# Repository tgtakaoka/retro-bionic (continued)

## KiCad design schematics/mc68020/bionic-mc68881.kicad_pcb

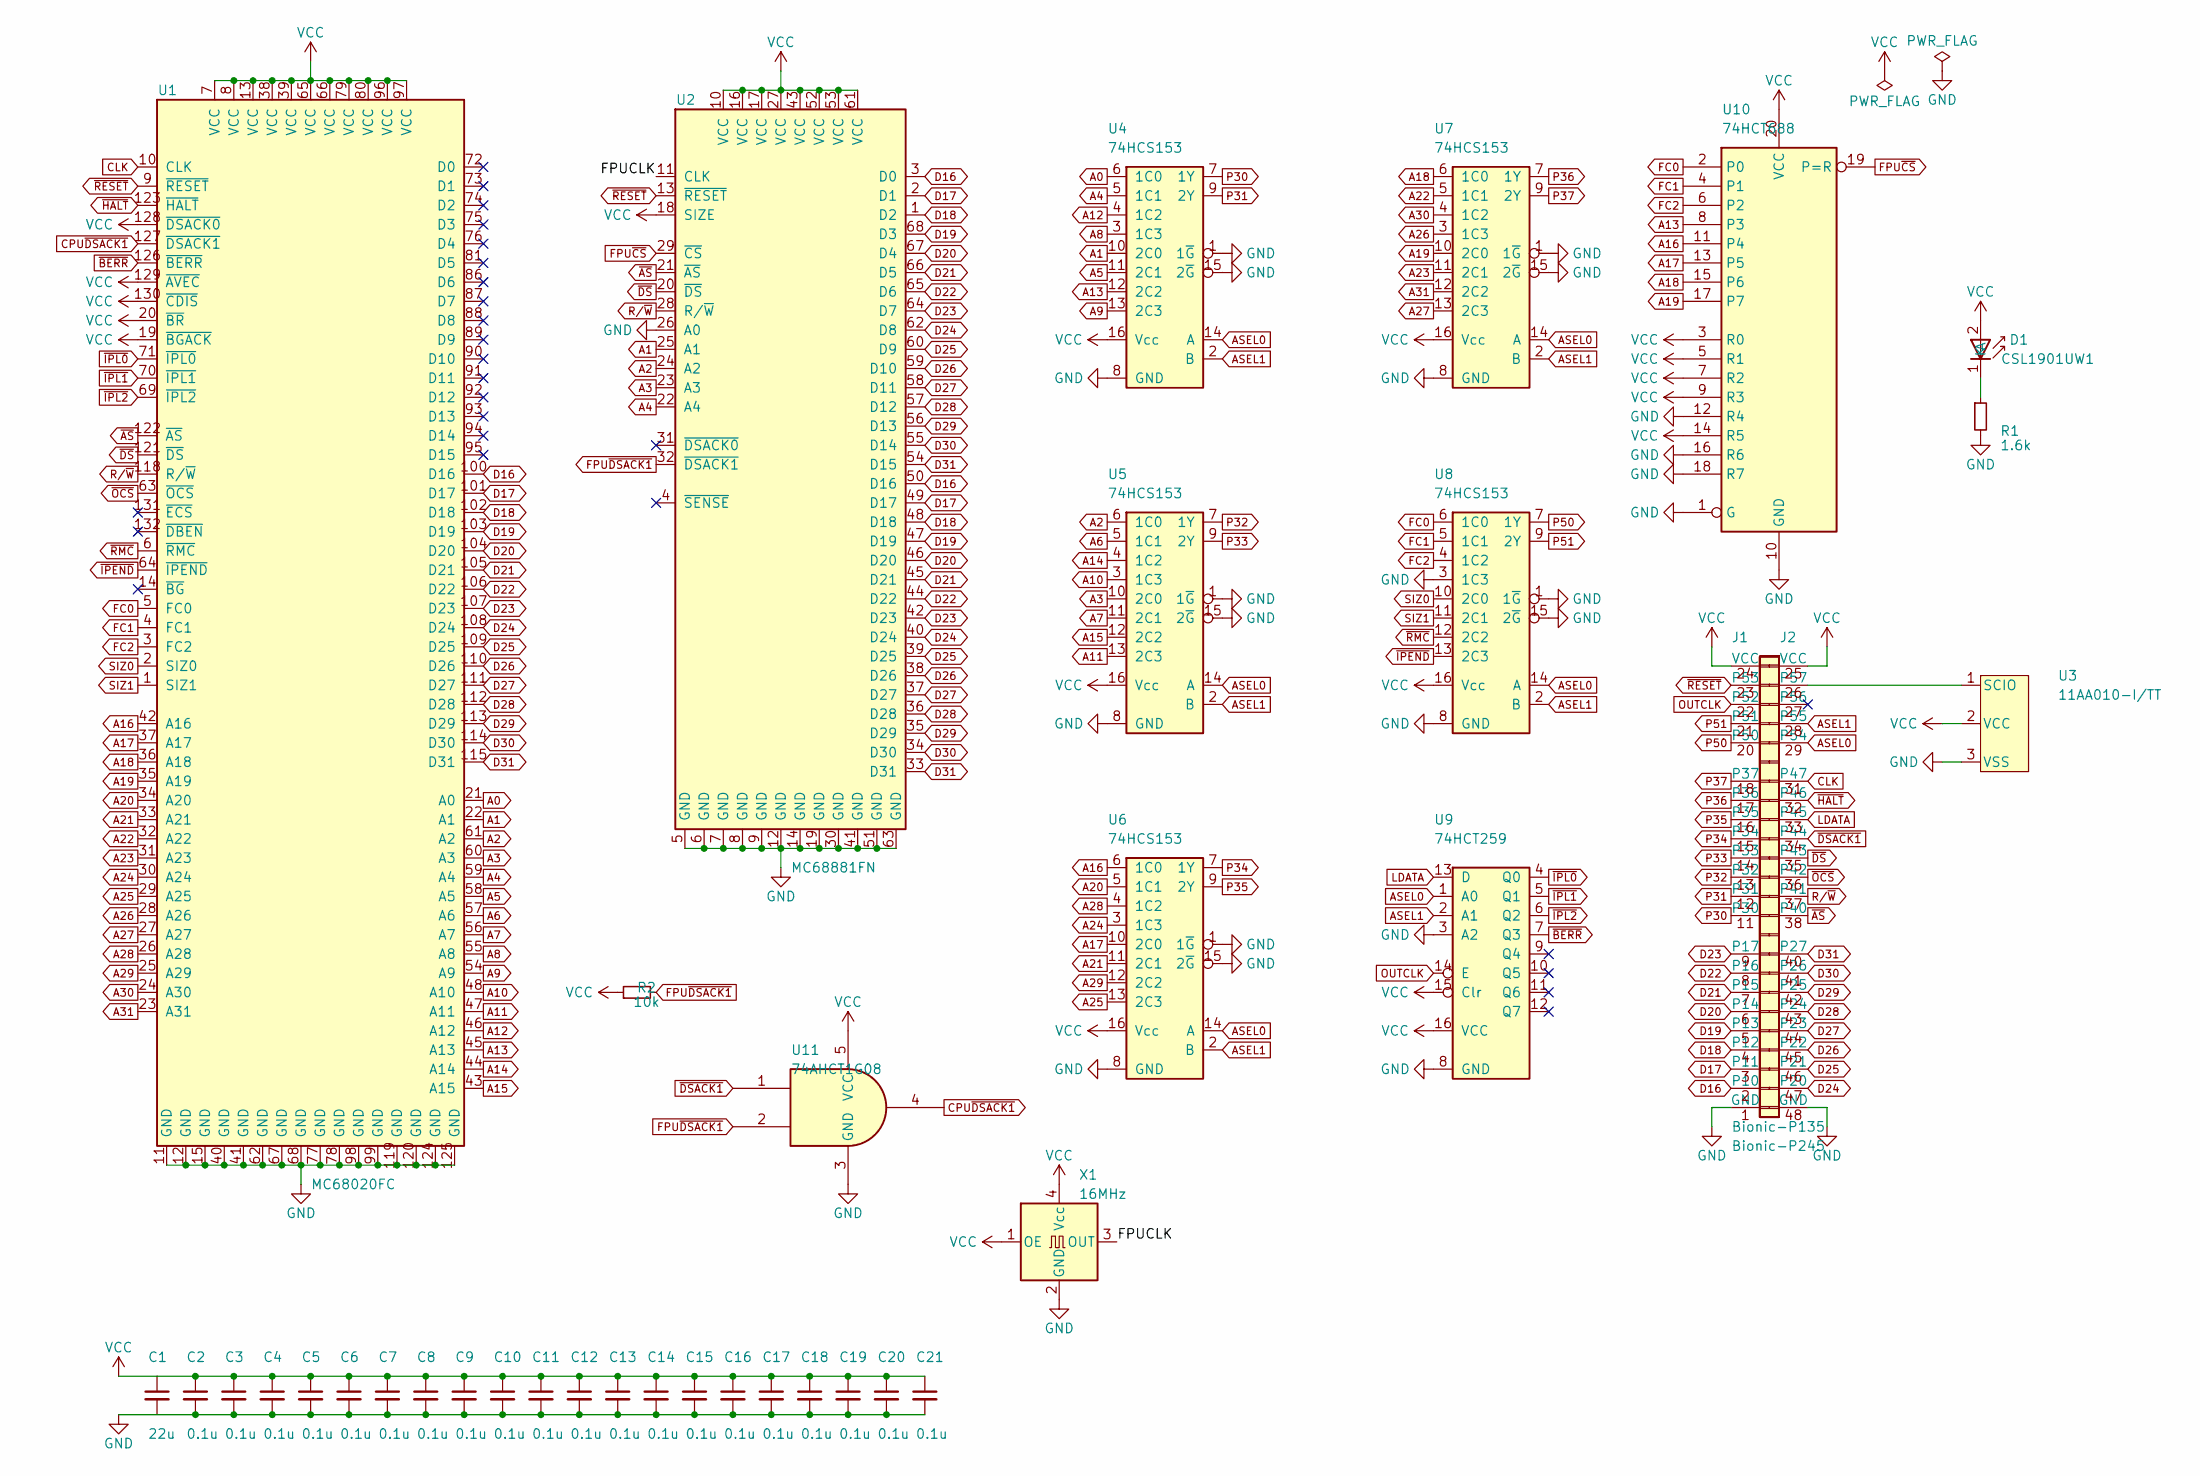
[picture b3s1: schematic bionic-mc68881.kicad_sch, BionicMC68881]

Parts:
C1: 22u; C_0603_1608Metric_Pad1.08x0.95mm_HandSolder
C2, C3, C4, C5, C6, C7, C8, C9, C10, C11, C12, C13, C14, C15, C16, C17, C18, C19, C20, C21: 0.1u; C_0603_1608Metric_Pad1.08x0.95mm_HandSolder
D1: CSL1901UW1; LED_CSL1901UW1_ROM-M
J1: Bionic-P135; Bionic-P135_SMT
J2: Bionic-P245; Bionic-P245_SMT
R1: 1.6k; R_0603_1608Metric_Pad0.98x0.95mm_HandSolder
R2: 10k; R_0603_1608Metric_Pad0.98x0.95mm_HandSolder
U1: MC68020FC; BQFP-132_24.13x24.13mm_P0.635mm_HandSoldering
U2: MC68881FN; PLCC-68_SMD-Socket
U3: 11AA010-I/TT; SOT-23_MC_MCH-M
U4, U5, U6, U7, U8: 74HCS153; PW16-M
U9: 74HCT259; TSSOP16_SOT403-1_NEX-M
U10: 74HCT688; PW20-M
U11: 74AHCT1G08; DBV5-M
X1: 16MHz; SX3M_3.2x2.5mm_HandSoldering

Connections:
/FPUCLK: U2.11 (CLK), X1.3 (OUT)
A0: U1.21 (A0), U4.6 (1C0)
A1: U1.22 (A1), U2.25 (A1), U4.10 (2C0)
A2: U1.61 (A2), U2.24 (A2), U5.6 (1C0)
A3: U1.60 (A3), U2.23 (A3), U5.10 (2C0)
A4: U1.59 (A4), U2.22 (A4), U4.5 (1C1)
A5: U1.58 (A5), U4.11 (2C1)
A6: U1.57 (A6), U5.5 (1C1)
A7: U1.56 (A7), U5.11 (2C1)
A8: U1.55 (A8), U4.3 (1C3)
A9: U1.54 (A9), U4.13 (2C3)
A10: U1.48 (A10), U5.3 (1C3)
A11: U1.47 (A11), U5.13 (2C3)
A12: U1.46 (A12), U4.4 (1C2)
A13: U1.45 (A13), U4.12 (2C2), U10.8 (P3)
A14: U1.44 (A14), U5.4 (1C2)
A15: U1.43 (A15), U5.12 (2C2)
A16: U1.42 (A16), U6.6 (1C0), U10.11 (P4)
A17: U1.37 (A17), U6.10 (2C0), U10.13 (P5)
A18: U1.36 (A18), U7.6 (1C0), U10.15 (P6)
A19: U1.35 (A19), U7.10 (2C0), U10.17 (P7)
A20: U1.34 (A20), U6.5 (1C1)
A21: U1.33 (A21), U6.11 (2C1)
A22: U1.32 (A22), U7.5 (1C1)
A23: U1.31 (A23), U7.11 (2C1)
A24: U1.30 (A24), U6.3 (1C3)
A25: U1.29 (A25), U6.13 (2C3)
A26: U1.28 (A26), U7.3 (1C3)
A27: U1.27 (A27), U7.13 (2C3)
A28: U1.26 (A28), U6.4 (1C2)
A29: U1.25 (A29), U6.12 (2C2)
A30: U1.24 (A30), U7.4 (1C2)
A31: U1.23 (A31), U7.12 (2C2)
ASEL0: J2.29 (P54), U4.14 (A), U5.14 (A), U6.14 (A), U7.14 (A), U8.14 (A), U9.1 (A0)
ASEL1: J2.28 (P55), U4.2 (B), U5.2 (B), U6.2 (B), U7.2 (B), U8.2 (B), U9.2 (A1)
CLK: J2.31 (P47), U1.10 (CLK)
CPU~DSACK1: U1.127 (~DSACK1), U11.4
D16: J1.2 (P10), U1.100 (D16), U2.3 (D0), U2.50 (D16)
D17: J1.3 (P11), U1.101 (D17), U2.2 (D1), U2.49 (D17)
D18: J1.4 (P12), U1.102 (D18), U2.1 (D2), U2.48 (D18)
D19: J1.5 (P13), U1.103 (D19), U2.47 (D19), U2.68 (D3)
D20: J1.6 (P14), U1.104 (D20), U2.46 (D20), U2.67 (D4)
D21: J1.7 (P15), U1.105 (D21), U2.45 (D21), U2.66 (D5)
D22: J1.8 (P16), U1.106 (D22), U2.44 (D22), U2.65 (D6)
D23: J1.9 (P17), U1.107 (D23), U2.42 (D23), U2.64 (D7)
D24: J2.47 (P20), U1.108 (D24), U2.40 (D24), U2.62 (D8)
D25: J2.46 (P21), U1.109 (D25), U2.39 (D25), U2.60 (D9)
D26: J2.45 (P22), U1.110 (D26), U2.38 (D26), U2.59 (D10)
D27: J2.44 (P23), U1.111 (D27), U2.37 (D27), U2.58 (D11)
D28: J2.43 (P24), U1.112 (D28), U2.36 (D28), U2.57 (D12)
D29: J2.42 (P25), U1.113 (D29), U2.35 (D29), U2.56 (D13)
D30: J2.41 (P26), U1.114 (D30), U2.34 (D30), U2.55 (D14)
D31: J2.40 (P27), U1.115 (D31), U2.33 (D31), U2.54 (D15)
FC0: U1.5 (FC0), U8.6 (1C0), U10.2 (P0)
FC1: U1.4 (FC1), U8.5 (1C1), U10.4 (P1)
FC2: U1.3 (FC2), U8.4 (1C2), U10.6 (P2)
FPU~CS: U2.29 (~CS), U10.19 (P=R)
FPU~DSACK1: R2.2, U2.32 (~DSACK1), U11.2
GND: C1.2, C2.2, C3.2, C4.2, C5.2, C6.2, C7.2, C8.2, C9.2, C10.2, C11.2, C12.2, C13.2, C14.2, C15.2, C16.2, C17.2, C18.2, C19.2, C20.2, C21.2, J1.1 (GND), J2.48 (GND), R1.2, U1.11 (GND), U1.12 (GND), U1.15 (GND), U1.40 (GND), U1.41 (GND), U1.62 (GND), U1.67 (GND), U1.68 (GND), U1.77 (GND), U1.78 (GND), U1.98 (GND), U1.99 (GND), U1.119 (GND), U1.120 (GND), U1.124 (GND), U1.125 (GND), U2.5 (GND), U2.6 (GND), U2.7 (GND), U2.8 (GND), U2.9 (GND), U2.12 (GND), U2.14 (GND), U2.19 (GND), U2.26 (A0), U2.30 (GND), U2.41 (GND), U2.51 (GND), U2.63 (GND), U3.3 (VSS), U4.1 (1~G), U4.8 (GND), U4.15 (2~G), U5.1 (1~G), U5.8 (GND), U5.15 (2~G), U6.1 (1~G), U6.8 (GND), U6.15 (2~G), U7.1 (1~G), U7.8 (GND), U7.15 (2~G), U8.1 (1~G), U8.3 (1C3), U8.8 (GND), U8.15 (2~G), U9.3 (A2), U9.8 (GND), U10.1 (G), U10.10 (GND), U10.12 (R4), U10.16 (R6), U10.18 (R7), U11.3 (GND), X1.2 (GND)
LDATA: J2.33 (P45), U9.13 (D)
unnamed: D1.1 (K), R1.1
unnamed: J2.26 (P57), U3.1 (SCIO)
OUTCLK: J1.22 (P52), U9.14 (E)
P30: J1.11 (P30), U4.7 (1Y)
P31: J1.12 (P31), U4.9 (2Y)
P32: J1.13 (P32), U5.7 (1Y)
P33: J1.14 (P33), U5.9 (2Y)
P34: J1.15 (P34), U6.7 (1Y)
P35: J1.16 (P35), U6.9 (2Y)
P36: J1.17 (P36), U7.7 (1Y)
P37: J1.18 (P37), U7.9 (2Y)
P50: J1.20 (P50), U8.7 (1Y)
P51: J1.21 (P51), U8.9 (2Y)
R/~W: J2.37 (P41), U1.118 (R/~W), U2.28 (R/~W)
SIZ0: U1.2 (SIZ0), U8.10 (2C0)
SIZ1: U1.1 (SIZ1), U8.11 (2C1)
VCC: C1.1, C2.1, C3.1, C4.1, C5.1, C6.1, C7.1, C8.1, C9.1, C10.1, C11.1, C12.1, C13.1, C14.1, C15.1, C16.1, C17.1, C18.1, C19.1, C20.1, C21.1, D1.2 (A), J1.24 (VCC), J2.25 (VCC), R2.1, U1.7 (VCC), U1.8 (VCC), U1.13 (VCC), U1.19 (~BGACK), U1.20 (~BR), U1.38 (VCC), U1.39 (VCC), U1.65 (VCC), U1.66 (VCC), U1.79 (VCC), U1.80 (VCC), U1.96 (VCC), U1.97 (VCC), U1.128 (~DSACK0), U1.129 (~AVEC), U1.130 (~CDIS), U2.10 (VCC), U2.16 (VCC), U2.17 (VCC), U2.18 (SIZE), U2.27 (VCC), U2.43 (VCC), U2.52 (VCC), U2.53 (VCC), U2.61 (VCC), U3.2 (VCC), U4.16 (Vcc), U5.16 (Vcc), U6.16 (Vcc), U7.16 (Vcc), U8.16 (Vcc), U9.15 (Clr), U9.16 (VCC), U10.3 (R0), U10.5 (R1), U10.7 (R2), U10.9 (R3), U10.14 (R5), U10.20 (VCC), U11.5 (VCC), X1.1 (OE), X1.4 (Vcc)
~AS: J2.38 (P40), U1.122 (~AS), U2.21 (~AS)
~BERR: U1.126 (~BERR), U9.7 (Q3)
~DSACK1: J2.34 (P44), U11.1
~DS: J2.35 (P43), U1.121 (~DS), U2.20 (~DS)
~HALT: J2.32 (P46), U1.123 (~HALT)
~IPEND: U1.64 (~IPEND), U8.13 (2C3)
~IPL0: U1.71 (~IPL0), U9.4 (Q0)
~IPL1: U1.70 (~IPL1), U9.5 (Q1)
~IPL2: U1.69 (~IPL2), U9.6 (Q2)
~OCS: J2.36 (P42), U1.63 (~OCS)
~RESET: J1.23 (P53), U1.9 (~RESET), U2.13 (~RESET)
~RMC: U1.6 (~RMC), U8.12 (2C2)

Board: 4 copper layers, 38 parts (22 on the bottom side), 89 nets, no tracks yet.

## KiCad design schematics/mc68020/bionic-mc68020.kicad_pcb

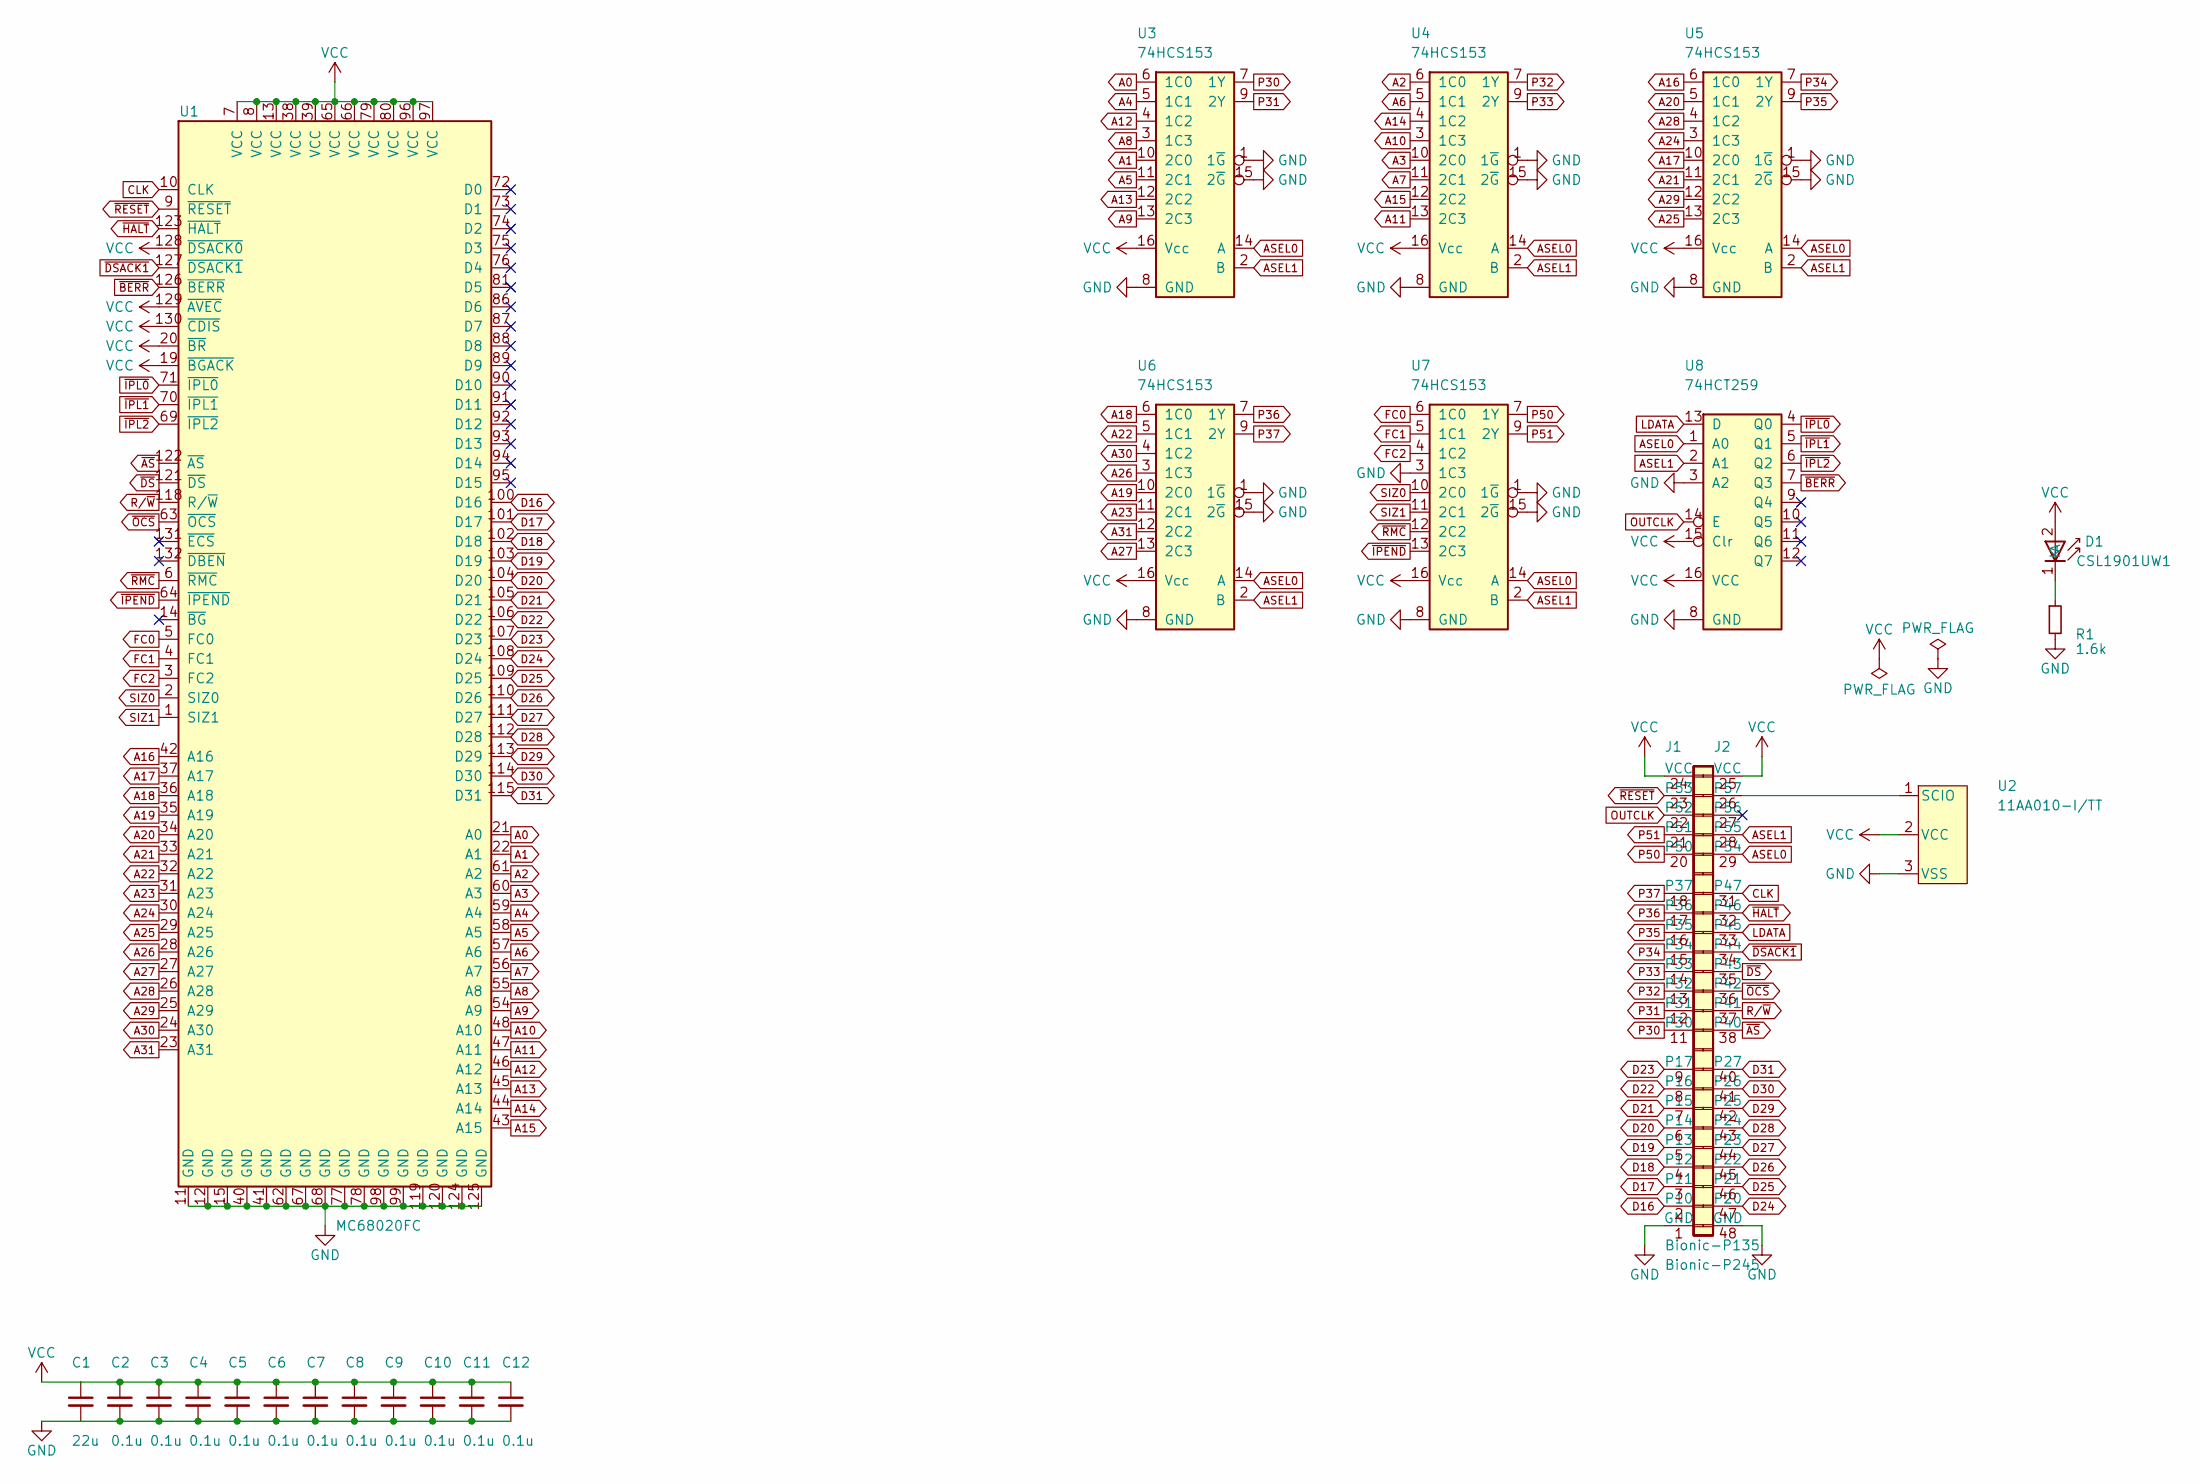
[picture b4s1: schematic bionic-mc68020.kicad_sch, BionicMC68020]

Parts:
C1: 22u; C_0603_1608Metric_Pad1.08x0.95mm_HandSolder
C2, C3, C4, C5, C6, C7, C8, C9, C10, C11, C12: 0.1u; C_0603_1608Metric_Pad1.08x0.95mm_HandSolder
D1: CSL1901UW1; LED_CSL1901UW1_ROM-M
J1: Bionic-P135; Bionic-P135_SMT
J2: Bionic-P245; Bionic-P245_SMT
R1: 1.6k; R_0603_1608Metric_Pad0.98x0.95mm_HandSolder
U1: MC68020FC; BQFP-132_24.13x24.13mm_P0.635mm_HandSoldering
U2: 11AA010-I/TT; SOT-23_MC_MCH-M
U3, U4, U5, U6, U7: 74HCS153; PW16-M
U8: 74HCT259; TSSOP16_SOT403-1_NEX-M

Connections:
A0: U1.21 (A0), U3.6 (1C0)
A1: U1.22 (A1), U3.10 (2C0)
A2: U1.61 (A2), U4.6 (1C0)
A3: U1.60 (A3), U4.10 (2C0)
A4: U1.59 (A4), U3.5 (1C1)
A5: U1.58 (A5), U3.11 (2C1)
A6: U1.57 (A6), U4.5 (1C1)
A7: U1.56 (A7), U4.11 (2C1)
A8: U1.55 (A8), U3.3 (1C3)
A9: U1.54 (A9), U3.13 (2C3)
A10: U1.48 (A10), U4.3 (1C3)
A11: U1.47 (A11), U4.13 (2C3)
A12: U1.46 (A12), U3.4 (1C2)
A13: U1.45 (A13), U3.12 (2C2)
A14: U1.44 (A14), U4.4 (1C2)
A15: U1.43 (A15), U4.12 (2C2)
A16: U1.42 (A16), U5.6 (1C0)
A17: U1.37 (A17), U5.10 (2C0)
A18: U1.36 (A18), U6.6 (1C0)
A19: U1.35 (A19), U6.10 (2C0)
A20: U1.34 (A20), U5.5 (1C1)
A21: U1.33 (A21), U5.11 (2C1)
A22: U1.32 (A22), U6.5 (1C1)
A23: U1.31 (A23), U6.11 (2C1)
A24: U1.30 (A24), U5.3 (1C3)
A25: U1.29 (A25), U5.13 (2C3)
A26: U1.28 (A26), U6.3 (1C3)
A27: U1.27 (A27), U6.13 (2C3)
A28: U1.26 (A28), U5.4 (1C2)
A29: U1.25 (A29), U5.12 (2C2)
A30: U1.24 (A30), U6.4 (1C2)
A31: U1.23 (A31), U6.12 (2C2)
ASEL0: J2.29 (P54), U3.14 (A), U4.14 (A), U5.14 (A), U6.14 (A), U7.14 (A), U8.1 (A0)
ASEL1: J2.28 (P55), U3.2 (B), U4.2 (B), U5.2 (B), U6.2 (B), U7.2 (B), U8.2 (A1)
CLK: J2.31 (P47), U1.10 (CLK)
D16: J1.2 (P10), U1.100 (D16)
D17: J1.3 (P11), U1.101 (D17)
D18: J1.4 (P12), U1.102 (D18)
D19: J1.5 (P13), U1.103 (D19)
D20: J1.6 (P14), U1.104 (D20)
D21: J1.7 (P15), U1.105 (D21)
D22: J1.8 (P16), U1.106 (D22)
D23: J1.9 (P17), U1.107 (D23)
D24: J2.47 (P20), U1.108 (D24)
D25: J2.46 (P21), U1.109 (D25)
D26: J2.45 (P22), U1.110 (D26)
D27: J2.44 (P23), U1.111 (D27)
D28: J2.43 (P24), U1.112 (D28)
D29: J2.42 (P25), U1.113 (D29)
D30: J2.41 (P26), U1.114 (D30)
D31: J2.40 (P27), U1.115 (D31)
FC0: U1.5 (FC0), U7.6 (1C0)
FC1: U1.4 (FC1), U7.5 (1C1)
FC2: U1.3 (FC2), U7.4 (1C2)
GND: C1.2, C2.2, C3.2, C4.2, C5.2, C6.2, C7.2, C8.2, C9.2, C10.2, C11.2, C12.2, J1.1 (GND), J2.48 (GND), R1.2, U1.11 (GND), U1.12 (GND), U1.15 (GND), U1.40 (GND), U1.41 (GND), U1.62 (GND), U1.67 (GND), U1.68 (GND), U1.77 (GND), U1.78 (GND), U1.98 (GND), U1.99 (GND), U1.119 (GND), U1.120 (GND), U1.124 (GND), U1.125 (GND), U2.3 (VSS), U3.1 (1~G), U3.8 (GND), U3.15 (2~G), U4.1 (1~G), U4.8 (GND), U4.15 (2~G), U5.1 (1~G), U5.8 (GND), U5.15 (2~G), U6.1 (1~G), U6.8 (GND), U6.15 (2~G), U7.1 (1~G), U7.3 (1C3), U7.8 (GND), U7.15 (2~G), U8.3 (A2), U8.8 (GND)
LDATA: J2.33 (P45), U8.13 (D)
unnamed: D1.1 (K), R1.1
unnamed: J2.26 (P57), U2.1 (SCIO)
OUTCLK: J1.22 (P52), U8.14 (E)
P30: J1.11 (P30), U3.7 (1Y)
P31: J1.12 (P31), U3.9 (2Y)
P32: J1.13 (P32), U4.7 (1Y)
P33: J1.14 (P33), U4.9 (2Y)
P34: J1.15 (P34), U5.7 (1Y)
P35: J1.16 (P35), U5.9 (2Y)
P36: J1.17 (P36), U6.7 (1Y)
P37: J1.18 (P37), U6.9 (2Y)
P50: J1.20 (P50), U7.7 (1Y)
P51: J1.21 (P51), U7.9 (2Y)
R/~W: J2.37 (P41), U1.118 (R/~W)
SIZ0: U1.2 (SIZ0), U7.10 (2C0)
SIZ1: U1.1 (SIZ1), U7.11 (2C1)
VCC: C1.1, C2.1, C3.1, C4.1, C5.1, C6.1, C7.1, C8.1, C9.1, C10.1, C11.1, C12.1, D1.2 (A), J1.24 (VCC), J2.25 (VCC), U1.7 (VCC), U1.8 (VCC), U1.13 (VCC), U1.19 (~BGACK), U1.20 (~BR), U1.38 (VCC), U1.39 (VCC), U1.65 (VCC), U1.66 (VCC), U1.79 (VCC), U1.80 (VCC), U1.96 (VCC), U1.97 (VCC), U1.128 (~DSACK0), U1.129 (~AVEC), U1.130 (~CDIS), U2.2 (VCC), U3.16 (Vcc), U4.16 (Vcc), U5.16 (Vcc), U6.16 (Vcc), U7.16 (Vcc), U8.15 (Clr), U8.16 (VCC)
~AS: J2.38 (P40), U1.122 (~AS)
~BERR: U1.126 (~BERR), U8.7 (Q3)
~DSACK1: J2.34 (P44), U1.127 (~DSACK1)
~DS: J2.35 (P43), U1.121 (~DS)
~HALT: J2.32 (P46), U1.123 (~HALT)
~IPEND: U1.64 (~IPEND), U7.13 (2C3)
~IPL0: U1.71 (~IPL0), U8.4 (Q0)
~IPL1: U1.70 (~IPL1), U8.5 (Q1)
~IPL2: U1.69 (~IPL2), U8.6 (Q2)
~OCS: J2.36 (P42), U1.63 (~OCS)
~RESET: J1.23 (P53), U1.9 (~RESET)
~RMC: U1.6 (~RMC), U7.12 (2C2)

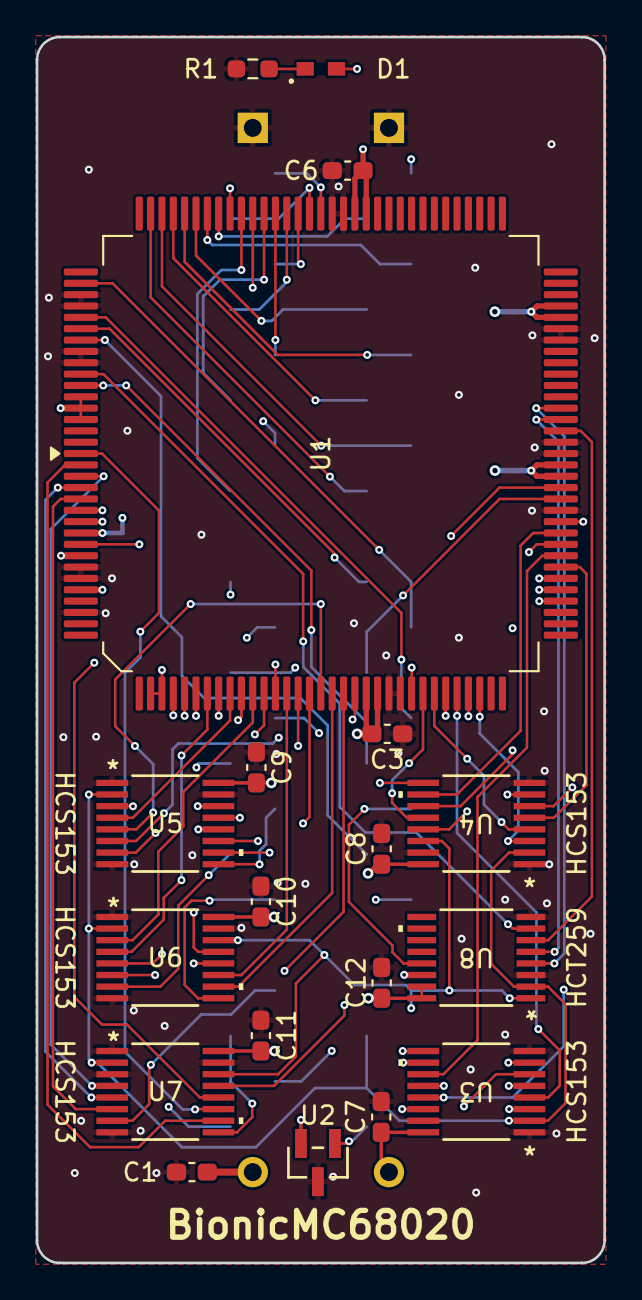
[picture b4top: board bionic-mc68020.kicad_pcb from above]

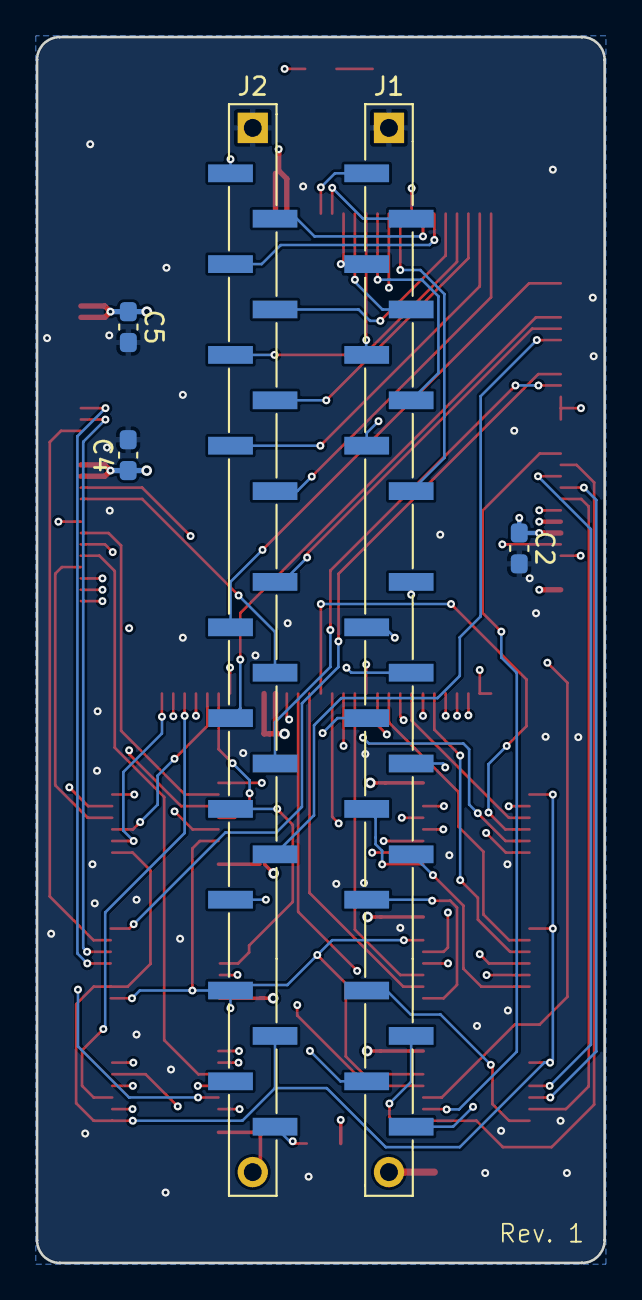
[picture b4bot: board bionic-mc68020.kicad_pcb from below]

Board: 4 copper layers, 31.7 x 68.6 mm, 24 parts (5 on the bottom side), 85 nets.

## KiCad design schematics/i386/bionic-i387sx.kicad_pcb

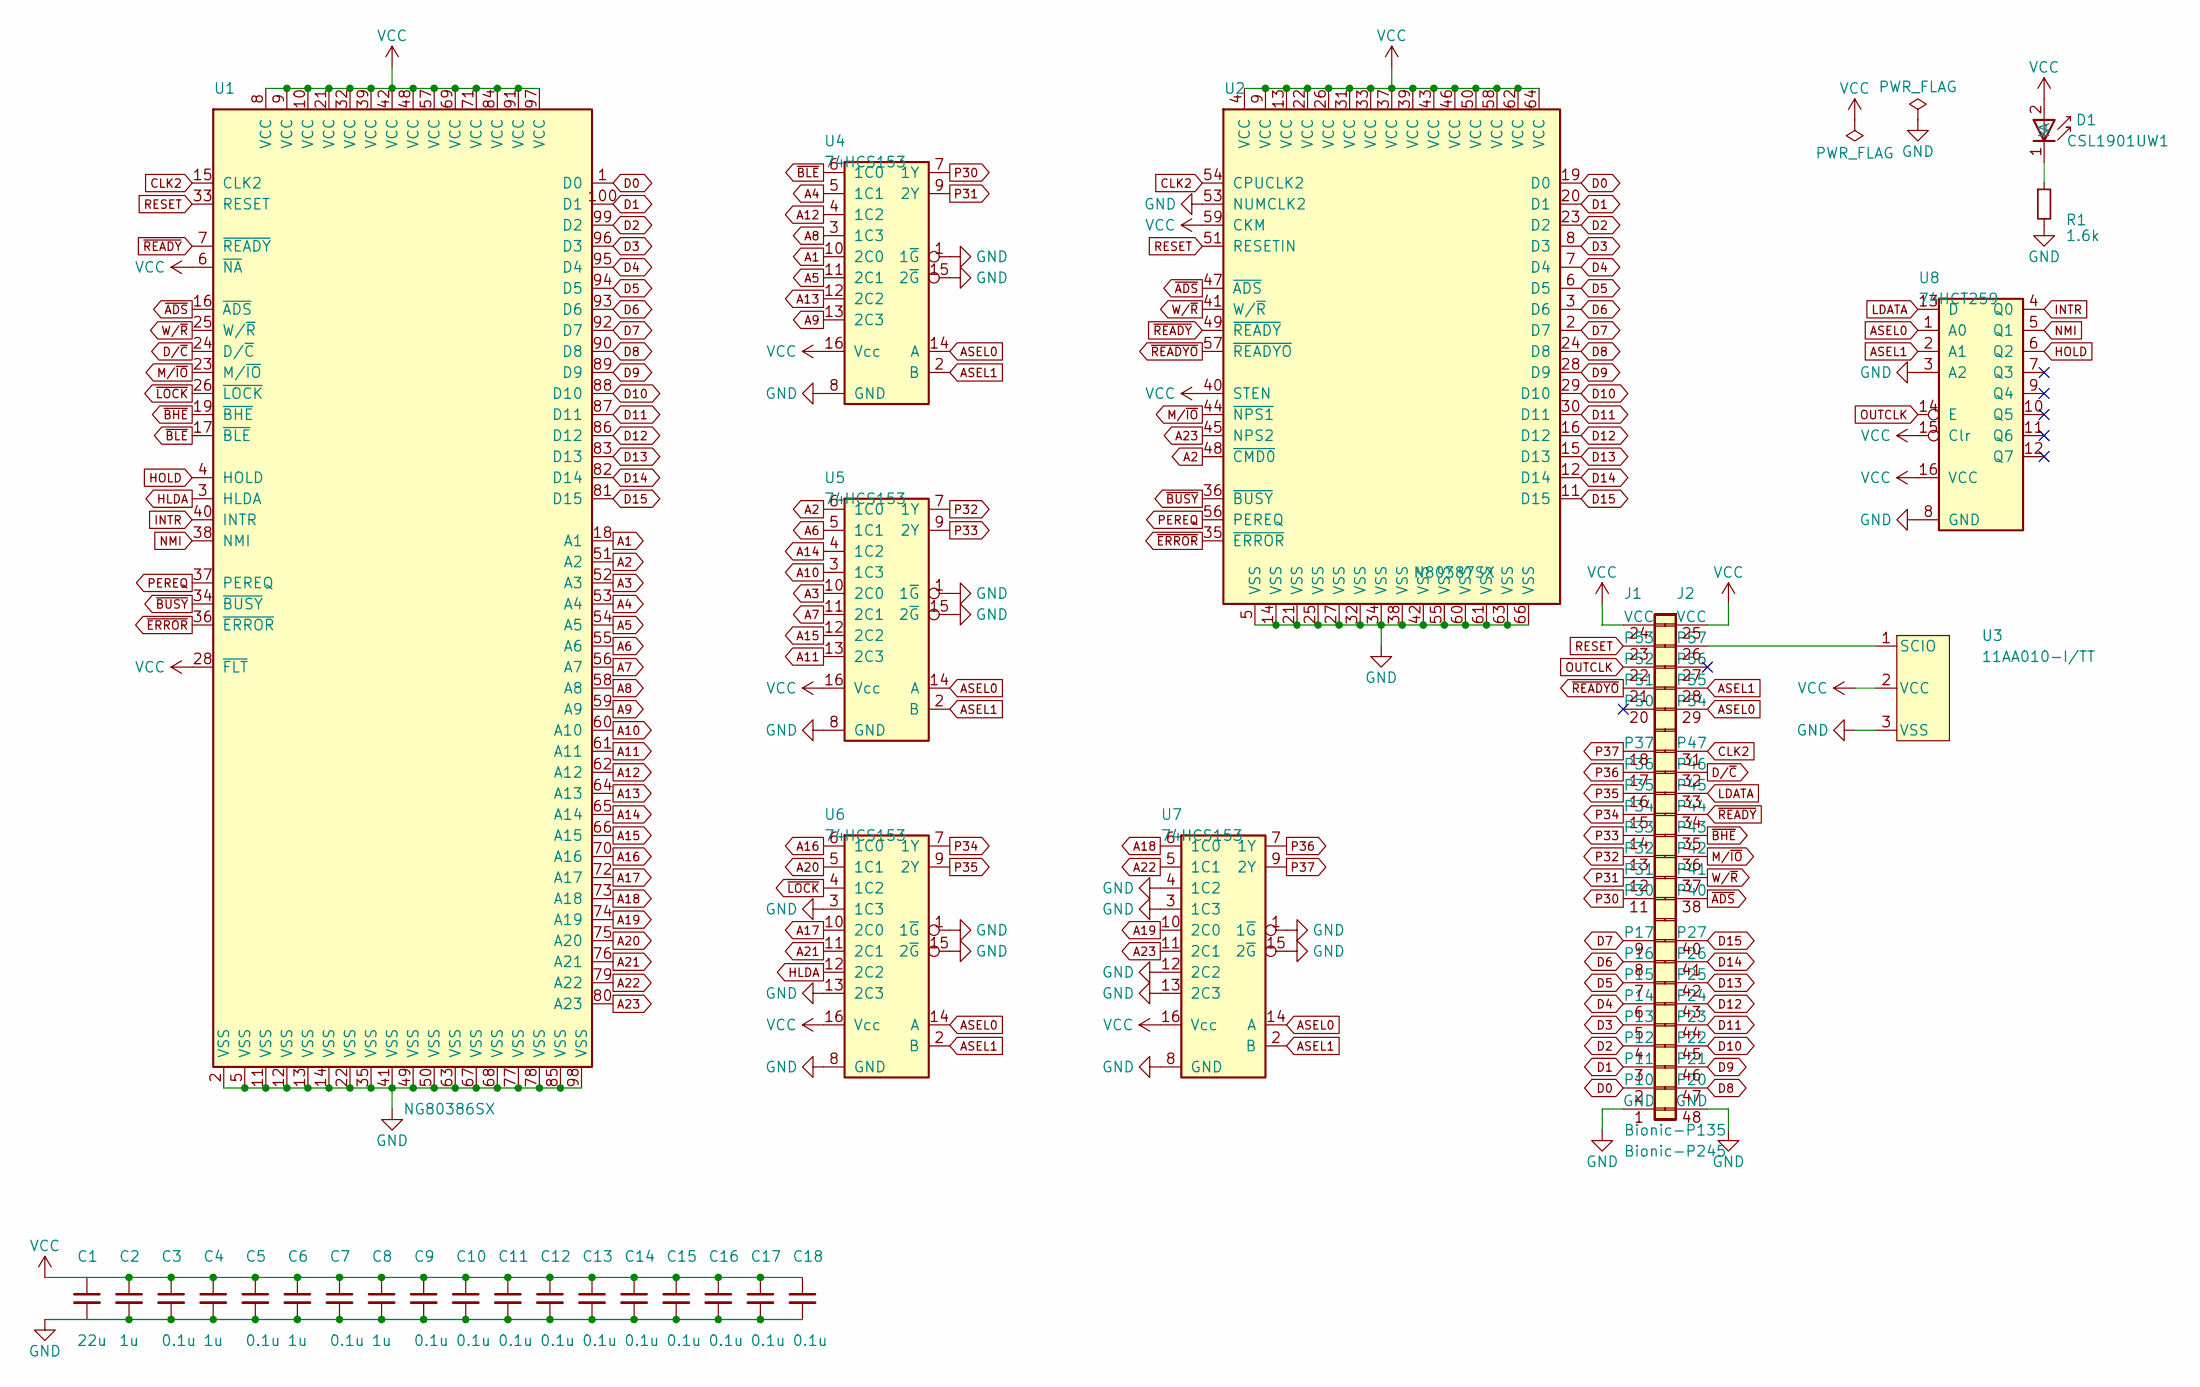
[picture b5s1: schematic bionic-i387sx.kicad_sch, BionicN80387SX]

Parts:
C1: 22u; C_0603_1608Metric_Pad1.08x0.95mm_HandSolder
C2, C4, C6, C8: 1u; C_0603_1608Metric_Pad1.08x0.95mm_HandSolder
C3, C5, C7, C9, C10, C11, C12, C13, C14, C15, C16, C17, C18: 0.1u; C_0603_1608Metric_Pad1.08x0.95mm_HandSolder
D1: CSL1901UW1; LED_CSL1901UW1_ROM-M
J1: Bionic-P135; Bionic-P135_SMT
J2: Bionic-P245; Bionic-P245_SMT
R1: 1.6k; R_0603_1608Metric_Pad0.98x0.95mm_HandSolder
U1: NG80386SX; BQFP-100_19.05x19.05mm_P0.635mm
U2: N80387SX; PLCC-68_SMD-Socket
U3: 11AA010-I/TT; SOT-23_MC_MCH-M
U4, U5, U6, U7: 74HCS153; PW16-M
U8: 74HCT259; TSSOP16_SOT403-1_NEX-M

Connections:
A1: U1.18 (A1), U4.10 (2C0)
A2: U1.51 (A2), U2.48 (~CMD0), U5.6 (1C0)
A3: U1.52 (A3), U5.10 (2C0)
A4: U1.53 (A4), U4.5 (1C1)
A5: U1.54 (A5), U4.11 (2C1)
A6: U1.55 (A6), U5.5 (1C1)
A7: U1.56 (A7), U5.11 (2C1)
A8: U1.58 (A8), U4.3 (1C3)
A9: U1.59 (A9), U4.13 (2C3)
A10: U1.60 (A10), U5.3 (1C3)
A11: U1.61 (A11), U5.13 (2C3)
A12: U1.62 (A12), U4.4 (1C2)
A13: U1.64 (A13), U4.12 (2C2)
A14: U1.65 (A14), U5.4 (1C2)
A15: U1.66 (A15), U5.12 (2C2)
A16: U1.70 (A16), U6.6 (1C0)
A17: U1.72 (A17), U6.10 (2C0)
A18: U1.73 (A18), U7.6 (1C0)
A19: U1.74 (A19), U7.10 (2C0)
A20: U1.75 (A20), U6.5 (1C1)
A21: U1.76 (A21), U6.11 (2C1)
A22: U1.79 (A22), U7.5 (1C1)
A23: U1.80 (A23), U2.45 (NPS2), U7.11 (2C1)
ASEL0: J2.29 (P54), U4.14 (A), U5.14 (A), U6.14 (A), U7.14 (A), U8.1 (A0)
ASEL1: J2.28 (P55), U4.2 (B), U5.2 (B), U6.2 (B), U7.2 (B), U8.2 (A1)
CLK2: J2.31 (P47), U1.15 (CLK2), U2.54 (CPUCLK2)
D0: J1.2 (P10), U1.1 (D0), U2.19 (D0)
D1: J1.3 (P11), U1.100 (D1), U2.20 (D1)
D2: J1.4 (P12), U1.99 (D2), U2.23 (D2)
D3: J1.5 (P13), U1.96 (D3), U2.8 (D3)
D4: J1.6 (P14), U1.95 (D4), U2.7 (D4)
D5: J1.7 (P15), U1.94 (D5), U2.6 (D5)
D6: J1.8 (P16), U1.93 (D6), U2.3 (D6)
D7: J1.9 (P17), U1.92 (D7), U2.2 (D7)
D8: J2.47 (P20), U1.90 (D8), U2.24 (D8)
D9: J2.46 (P21), U1.89 (D9), U2.28 (D9)
D10: J2.45 (P22), U1.88 (D10), U2.29 (D10)
D11: J2.44 (P23), U1.87 (D11), U2.30 (D11)
D12: J2.43 (P24), U1.86 (D12), U2.16 (D12)
D13: J2.42 (P25), U1.83 (D13), U2.15 (D13)
D14: J2.41 (P26), U1.82 (D14), U2.12 (D14)
D15: J2.40 (P27), U1.81 (D15), U2.11 (D15)
D/~C: J2.32 (P46), U1.24 (D/~C)
GND: C1.2, C2.2, C3.2, C4.2, C5.2, C6.2, C7.2, C8.2, C9.2, C10.2, C11.2, C12.2, C13.2, C14.2, C15.2, C16.2, C17.2, C18.2, J1.1 (GND), J2.48 (GND), R1.2, U1.2 (VSS), U1.5 (VSS), U1.11 (VSS), U1.12 (VSS), U1.13 (VSS), U1.14 (VSS), U1.22 (VSS), U1.35 (VSS), U1.41 (VSS), U1.49 (VSS), U1.50 (VSS), U1.63 (VSS), U1.67 (VSS), U1.68 (VSS), U1.77 (VSS), U1.78 (VSS), U1.85 (VSS), U1.98 (VSS), U2.5 (VSS), U2.14 (VSS), U2.21 (VSS), U2.25 (VSS), U2.27 (VSS), U2.32 (VSS), U2.34 (VSS), U2.38 (VSS), U2.42 (VSS), U2.53 (NUMCLK2), U2.55 (VSS), U2.60 (VSS), U2.61 (VSS), U2.63 (VSS), U2.66 (VSS), U3.3 (VSS), U4.1 (1~G), U4.8 (GND), U4.15 (2~G), U5.1 (1~G), U5.8 (GND), U5.15 (2~G), U6.1 (1~G), U6.3 (1C3), U6.8 (GND), U6.13 (2C3), U6.15 (2~G), U7.1 (1~G), U7.3 (1C3), U7.4 (1C2), U7.8 (GND), U7.12 (2C2), U7.13 (2C3), U7.15 (2~G), U8.3 (A2), U8.8 (GND)
HLDA: U1.3 (HLDA), U6.12 (2C2)
HOLD: U1.4 (HOLD), U8.6 (Q2)
INTR: U1.40 (INTR), U8.4 (Q0)
LDATA: J2.33 (P45), U8.13 (D)
M/~IO: J2.36 (P42), U1.23 (M/~IO), U2.44 (~NPS1)
NMI: U1.38 (NMI), U8.5 (Q1)
unnamed: D1.1 (K), R1.1
unnamed: J2.26 (P57), U3.1 (SCIO)
OUTCLK: J1.22 (P52), U8.14 (E)
P30: J1.11 (P30), U4.7 (1Y)
P31: J1.12 (P31), U4.9 (2Y)
P32: J1.13 (P32), U5.7 (1Y)
P33: J1.14 (P33), U5.9 (2Y)
P34: J1.15 (P34), U6.7 (1Y)
P35: J1.16 (P35), U6.9 (2Y)
P36: J1.17 (P36), U7.7 (1Y)
P37: J1.18 (P37), U7.9 (2Y)
PEREQ: U1.37 (PEREQ), U2.56 (PEREQ)
RESET: J1.23 (P53), U1.33 (RESET), U2.51 (RESETIN)
VCC: C1.1, C2.1, C3.1, C4.1, C5.1, C6.1, C7.1, C8.1, C9.1, C10.1, C11.1, C12.1, C13.1, C14.1, C15.1, C16.1, C17.1, C18.1, D1.2 (A), J1.24 (VCC), J2.25 (VCC), U1.6 (~NA), U1.8 (VCC), U1.9 (VCC), U1.10 (VCC), U1.21 (VCC), U1.28 (~FLT), U1.32 (VCC), U1.39 (VCC), U1.42 (VCC), U1.48 (VCC), U1.57 (VCC), U1.69 (VCC), U1.71 (VCC), U1.84 (VCC), U1.91 (VCC), U1.97 (VCC), U2.4 (VCC), U2.9 (VCC), U2.13 (VCC), U2.22 (VCC), U2.26 (VCC), U2.31 (VCC), U2.33 (VCC), U2.37 (VCC), U2.39 (VCC), U2.40 (STEN), U2.43 (VCC), U2.46 (VCC), U2.50 (VCC), U2.58 (VCC), U2.59 (CKM), U2.62 (VCC), U2.64 (VCC), U3.2 (VCC), U4.16 (Vcc), U5.16 (Vcc), U6.16 (Vcc), U7.16 (Vcc), U8.15 (Clr), U8.16 (VCC)
W/~R: J2.37 (P41), U1.25 (W/~R), U2.41 (W/~R)
~ADS: J2.38 (P40), U1.16 (~ADS), U2.47 (~ADS)
~BHE: J2.35 (P43), U1.19 (~BHE)
~BLE: U1.17 (~BLE), U4.6 (1C0)
~BUSY: U1.34 (~BUSY), U2.36 (~BUSY)
~ERROR: U1.36 (~ERROR), U2.35 (~ERROR)
~LOCK: U1.26 (~LOCK), U6.4 (1C2)
~READYO: J1.21 (P51), U2.57 (~READYO)
~READY: J2.34 (P44), U1.7 (~READY), U2.49 (~READY)

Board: 4 copper layers, 30 parts (9 on the bottom side), 73 nets, no tracks yet.
